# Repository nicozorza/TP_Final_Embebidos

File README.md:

# TP_Final_Embebidos
El TP final de Seminario de Sistemas Embebidos consiste en realizar el control de temperatura para un horno SMD.

###################################################################################################
## Avances con el ADC
* Chip_ADC_Init: Hace una configuracion por default del ADC. Recibe LPC_AD0 o LPC_ADC1, y un puntero a una estructura
	del tipo ADC_CLOCK_SETUP_T que es la que contiene toda la informacion de la configuracion.	
* Chip_ADC_EnableChannel: Habilita un determinado canal del ADC. Recibe LPC_ADC0 o LPC_ADC1, el canal del ADC a utilizar (ADC_CH0-7).
* NVIC_EnableIRQ: Agrega las interrupciones del ADC al vector de interrupciones. Recibe ADC0_IRQn o ADC1_IRQn. 
	El handler es ADC0_IRQHandler o ADC1_IRQHandler.
* Chip_ADC_Int_SetChannelCmd: Habilita o desabilita las interrupciones de un terminado canal del ADC.
* Chip_ADC_SetBurstCmd: Este modo realiza conversiones a maxima velocidad. Apenas termina una conversión comienza otra. Por esta razón,
	si se desean leer los valores convertidos es necesario parar las conversiones en la interrupcion, ya que la velocidad de las
	conversiones no permiten realizar otras actividades (la interrupcion salta todo el tiempo). Este modo permite tambien hacer
	conversiones de todos los canales al mismo tiempo (primero convierte ADC0, luego ADC1 y asi. Convierte los canales activados),
	lo cual evita tener que multiplexar. Hay que tener cuidado porque las sucesivas conversiones se van pisando, asi que hay que 
	leerlas rapido.
* Chip_ADC_SetStartMode: Comienza una conversión del ADC. Permite seleccionar si la conversion quiere hacerse inmediatamente o con
	alguna señal de trigger.
	
### OBSERVACIONES: 
* Usando el StartMode, luego de cada conversión es necesario volver a habilitar el StartMode para realizar una nueva conversión.

###################################################################################################
## Avances con la salida PWM
El bloque PWM tiene 2 salidas (con polaridades opuestas), cada una con 3 canales: MCOA0/1/2 y MCOB0/1/2. Tiene tambien dos canales
de entrada que permiten generar un trigger.
Cada canal tiene un TC(Timer/Counter), el cual es comparado con un "Limit Register", y cuando coinciden, el TC se resetea de dos formas
diferentes:
* En el modo "Edge aligned Mode" el TC se resetea a cero.
* En el modo "Centered Mode" el TC invierte su sentido, y comienza a decrementarse hasta llegar a cero, donde vuelve a incremenetarse.
Cada canal tiene tambien un "Match Register", que tiene un valor menor al Limit Register:
* En el modo "Edge aligned Mode" las salidas se switchean siempre que se alcance el Match o el Limit Register.
* En el modo "Centered Mode" las salidas se switchean unicamente cuando se alcanza el Match Register.

Por lo tanto, el Limit Register controla el periodo mientras que el Match Register el duty cycle.
Al parecer esta libreria no esta implementada, pero lo que si esta es una adaptacion del SCT como PWM. En esta pagina hay información
para configurar el bloque SCT como PWM http://www.lpcware.com/content/faq/how-use-sct-standard-pwm-using-lpcopen. 
Para configurar este bloque se debe hacer:
1) Chip_SCTPWM_Init(LPC_SCT): Habilita un clock externo.
2) Chip_SCTPWM_SetRate(LPC_SCT, SCT_PWM_RATE): Se configura la frecuencia del SCT.
3) Se debe configurar el SCU de los pines a utilizar con Chip_SCU_PinMuxSet(). Las salidas del SCT estan conectadas a los pines 
	CTOUT_n (P4_2, P4_1, P2_10, P4_3, P2_12, P2_11, P1_2, P1_1,...).
4) Configurar el output pin correspondiente con Chip_SCTPWM_SetOutPin(LPC_SCT, index, pin), donde index es un numero que va de 1 a N,
	siendo N la cantidad de pines de salida o de Match Registers (el minimo de los dos), y pin es el pin de CTOUT a configurar.
5) Se configura el duty cycle con Chip_SCTPWM_SetDutyCycle(LPC_SCT, index, ticks), donde ticks indica la cantidad de ticks en que la 
	salida permanece encendida. Utilizando Chip_SCTPWM_PercentageToTicks(LPC_SCT, percent) se puede setear el duty cycle mediante
	porcentajes sobre el total.
6) Se inicia el PWM con Chip_SCTPWM_Start(LPC_SCT).
7) El PWM se detiene con Chip_SCTPWM_Stop(LPC_SCT).

### OBSERVACIONES:
* Chip_SCT_EnableEventInt(LPC_SCT_T *pSCT, CHIP_SCT_EVENT_T evt) permite habilitar las interrupciones de acuerdo a los eventos. El
	handler es SCT_IRQHandler(). Los posibles eventos son: match condition, input o output condition, combinaciones de ambos.
* El tema de las interrupciones no me funciono todavia, pero todo lo otro al parecer funciona perfectamente. Tendria que ver si logro
	hacer andar el pwm de la forma original.
		
###################################################################################################

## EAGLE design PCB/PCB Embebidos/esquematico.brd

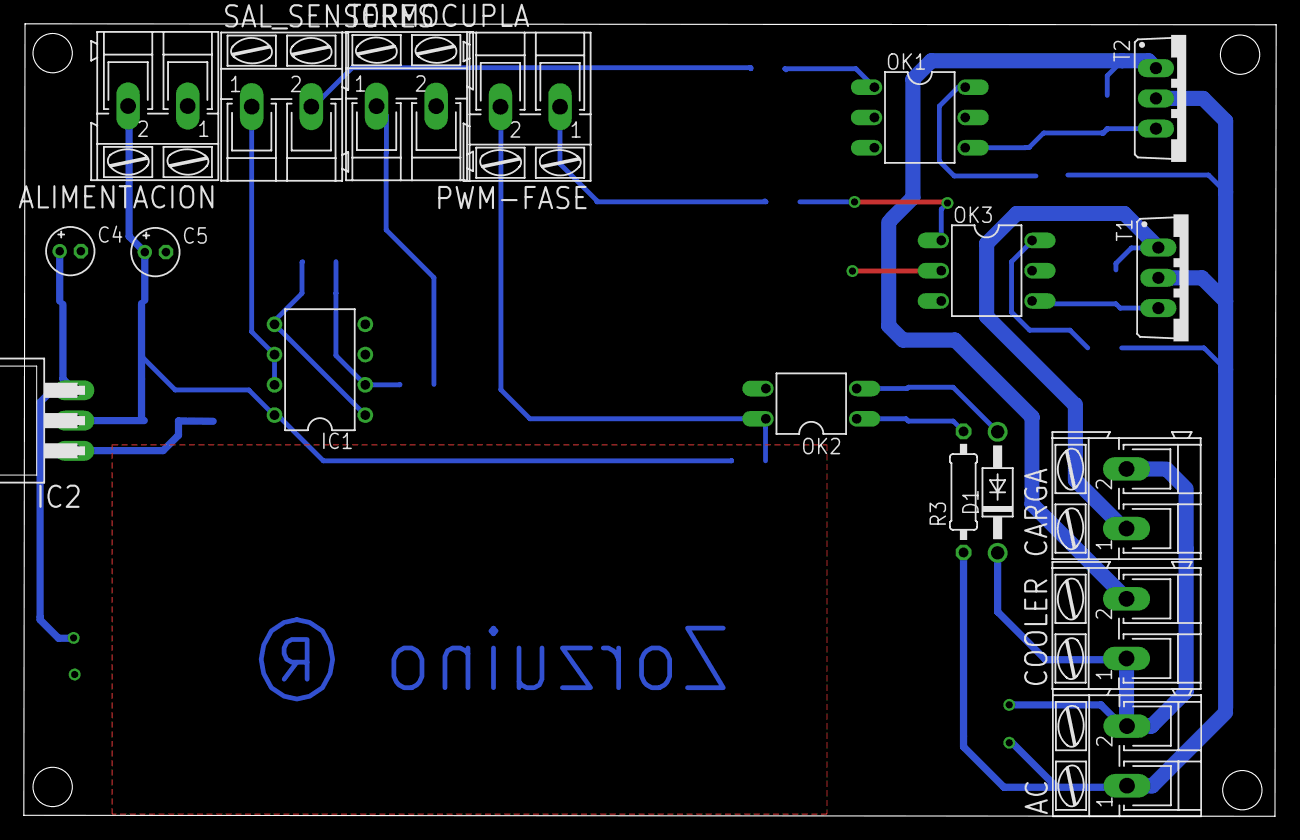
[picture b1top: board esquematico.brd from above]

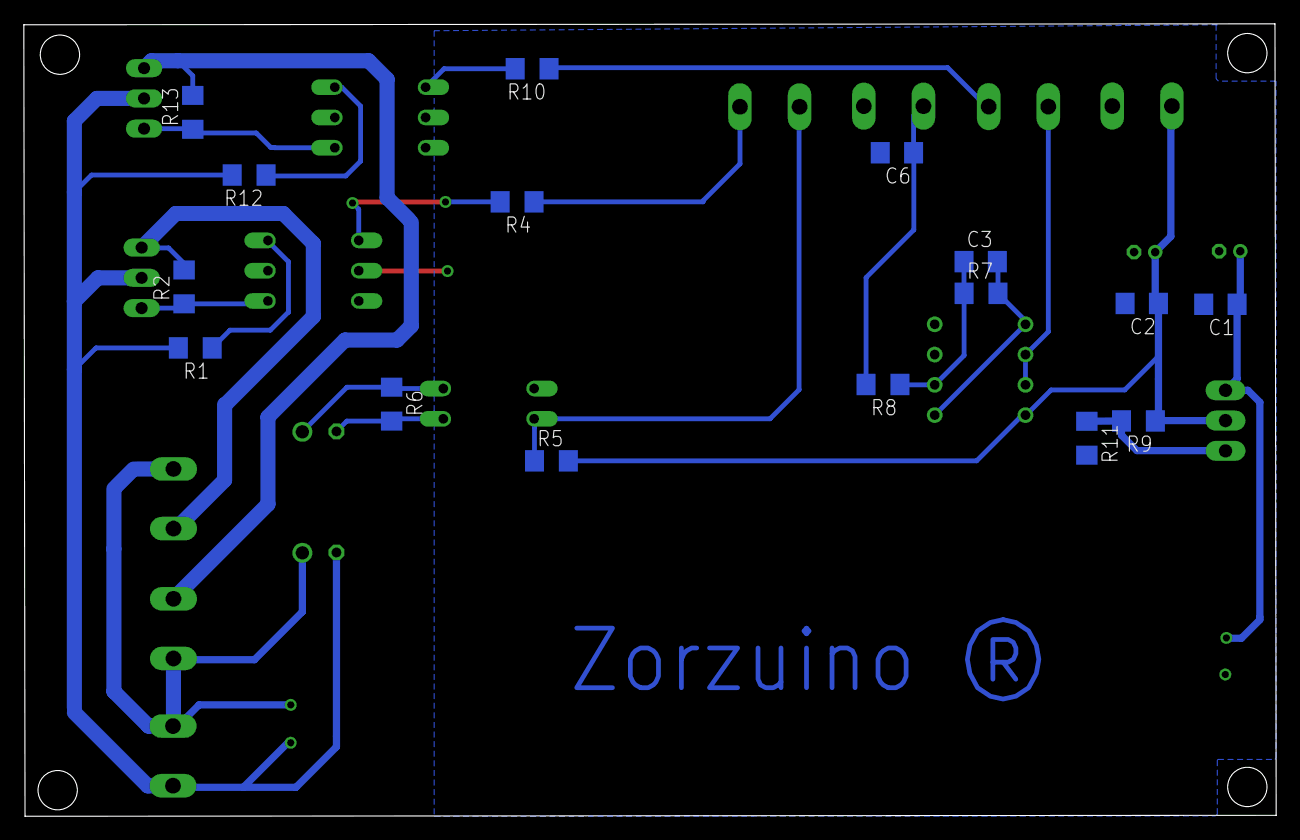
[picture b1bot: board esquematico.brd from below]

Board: 2 copper layers, 105.1 x 66.5 mm, 34 parts (16 on the bottom side), 23 nets.

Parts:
AC: AK300/2
ALIMENTACION: AK300/2
C1, C2, C3, C6: 100n; C1206
C4, C5: 100u; E1,8-4
CARGA: AK300/2
COOLER: AK300/2
D1: 1N4004; DO41-10
IC1: LM358N; DIL08
IC2: 317T; TO220H
OK1, OK3: MOC3031M; DIL06
OK2: PC817; DIL04
PWM-FASE: AK300/2
R1, R2, R12, R13: 330; R1206
R3: 20k; 0207/10
R4, R10: 680; R1206
R5, R8: 1k; R1206
R6: 100k; R1206
R7: 250k; R1206
R9: 340=680/2; R1206
R11: 560; R1206
SAL_SENSORES: AK300/2
T1, T2: BT138-V; TO220BV
TERMOCUPLA: AK300/2

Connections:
AC+: AC.1, R1.2, R3.1, R12.2, T1.T2, T2.T2
AC-: AC.2, CARGA.2, COOLER.1, D1.C
COOLER_PIN: R10.1, SAL_SENSORES.2
FASE: OK2.4, PWM-FASE.2, R5.1
GND: ALIMENTACION.1, C1.2, C2.2, C4.-, C5.-, C6.2, IC1.3, IC1.4, OK1.2, OK2.3, OK3.2, R11.2, TERMOCUPLA.2
unnamed: OK3.1, R4.2
unnamed: OK3.6, R1.1
unnamed: OK2.1, R3.2, R6.2
unnamed: CARGA.1, R2.2, T1.T1
unnamed: C3.1, IC1.2, R7.1, R8.1
unnamed: IC2.1, R9.2, R11.1
unnamed: C3.2, IC1.1, IC1.5, R7.2
unnamed: OK3.4, R2.1, T1.G
unnamed: D1.A, OK2.2, R6.1
unnamed: OK1.1, R10.2
unnamed: OK1.6, R12.1
unnamed: OK1.4, R13.1, T2.G
unnamed: COOLER.2, R13.2, T2.T1
PWM: PWM-FASE.1, R4.1
SAL_TERMOCUPLA: IC1.6, IC1.7, SAL_SENSORES.1
TERMOCUPLA: C6.1, R8.2, TERMOCUPLA.1
VCC: ALIMENTACION.2, C2.1, C5.+, IC1.8, IC2.2, R5.2, R9.1
VCC_5V: C1.1, C4.+, IC2.3

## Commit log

2017-05-05 Empece el proyecto de prueba del puerto serie, donde la idea es armar las librerias para no tener que utilizar DEBUGOUT, etc.
2017-05-05 Hay algun lio con los pines del SCU porque no coinciden con los de la hoja de datos, y por eso solo me anda el UART2 y no los demas
2017-05-06 Empece a probar el ADC. El problema con el puerto serie es que la UART2 es la que esta conectada a la salida USB, entonces para probar los demas puertos de USB tengo que conectar el conversor. Esto l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
2017-05-06 Borro todo porque por alguna razon me quedo todo mal configurado. Vuelvo a empezar
2017-05-06 Probe el ejemplo del adc importado. No encontre porque no me andaba el puerto serie antes, pero mañana lo voy a revisar. Seguro que estoy creando mal el proyecto desde el inicio y por eso explota
2017-05-06 No pude crear un proyecto para probar el ADC desde cero, asi que termine copiando un proyecto ya creado.
2017-05-06 Agrego informacion sobre el BurstMode del ADC
2017-05-06 Empece a probar el pwm. Simplemente importe el ejemplo que hay, pero creo que sin osciloscopio no voy a poder ver bien como funciona. Voy a probar midiendo el valor medio.
2017-05-07 Estuve investigando sobre la generacion de PWM, y agregando datos al readme.md. Estaba viendo sobre el tema de las interrupciones del sct pero me voy a jugar al fulbito
2017-05-08 Al parecer ya anda el PWM (configurandolo segun lo que puse en el README.md). Faltaria averiguar sobre el tema de las interrupciones del pwm y de la otra configuracion que esta en el datasheet. El si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
2017-05-09 Empece a armar un proyecto de prueba para un controlador PID. La idea es poner un pote y ver si funciona: Entro con tension y salgo con pwm. Si esto funciona ya puedo probar de controlar la temperatu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
2017-05-09 Lo que hice fue leer un valor del adc, y utilizarlo para modificar el valor de PWM en un rango entre 0-100%. Esto funciono perfectamente, asi que tengo que ver que onda lo del PID (todavia la placa n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
2017-05-09 Agregue una pequeña simulacion para un controlador PID de tiempo discreto, ya que nunca habia hecho nada de eso. Parece funcionar bien, pero no hice ninguna cuenta asi que esta puesto todo a ojo
2017-05-09 Supuestamente deje todo listo para probar el PID: Hay que cerrar el lazo de realimentacion y ver si funciona. Cuando tenga la bornera hay la prueba posta
2017-05-10 Probe el PID por software y anduvo hermoso. Ahora falta cerrar el lazo de forma física, y ya va a estar todo listo para hacer el control de temperatura
2017-05-10 Modifique unas cositas para que quede mas prolijo el README.md
2017-05-19 Arme los circuitos de deteccion de fase y disparo del tiristor. Cree un proyecto (Prueba_detectar_fase) donde activo las interrupcione de entrada de un pin (para detectar los cruces), meto un delay, 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
2017-05-19 Agregue un proyecto cabeza que utiliza interrupciones en un pin de entrada para sincronizar una senoidal con lo que seria el disparo del gate del triac (Prueba_detectar_fase). Funciono perfectamente,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
2017-05-21 Arme el proyecto Prueba_cambiar_valor_eficaz, donde lo que hago es con un pote variar la tension de un canal del adc, y en funcion de esa tension cambio el valor eficaz de la altera. Para esto lo que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
2017-05-22 Empece a hacer el esquematico. No se si hacer un poncho o una placa separada, porque no me gusta mucho la idea de tener la potencia cerca del micro, a pesar de tener todo con optoacopladores
2017-05-22 Reorganice el proyecto un poco porque estaba todo re tirado
2017-05-22 Empece a escribir el codigo en FreeRTOS. Mas o menos ya pase todo lo que habia hecho antes de forma cabeza, y ahora estoy viendo el tema de la configuracion del timer. Me voy a almorzar y despues sigo
2017-05-22 Modifique algunas cosas en la parte del trigger. Me parece que conviene probar bien todo antes de seguir avanzando, porque me genera dudas los retardos que puede meter el scheduler
2017-05-23 No me habia dado cuenta, pero las librerias que estaba importando tenian la frecuencia del clock dividida por 4. Eso se lo saque, ya que necesito hacer todo a la mayor velocidad posible
2017-05-23 Empece a probar el codigo de FreeRTOS con el circuito. Cada tanto se cuelga, pero no encuentro la razon (el codigo salta a un handler por default, pero lo hace antes de entrar al codigo posta). Esta 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
2017-05-23 No logre ningun resultado positivo con las funciones bloqueantes de FreeRTOS. Ahora esta puesto un delay con un while, pero estuve ajustando algunos numeros para que funcione mejor
2017-05-24 Probe algunas cosas con el sensor de temperatura. Arme un proyectito bien choto que lee el ADC (donde esta conectado el circuito del sensor de temperatura) y lo manda por el puerto serie
2017-05-24 Agregue el circuito de la termocupla al esquematico de Eagle. Falta definir si vamos a meter el PT100 como referencia
2017-05-24 Agregue unas cosas para los sensores de temperatura. No pude hacer bien la calibracion con el pt100, porque ambos sensores miden la misma temperatura (supuestamente la suma de ambas temperaturas da l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
2017-05-24 Agregue al PCB un regulador de 3.3v porque la EDU-CIAA labura con esa tension, y sino iba a tener problemas con el ADC. Tendria que probar que la parte de control siga funcionando bien, pero segun la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
2017-05-25 Estuve probando de hacer el delay del trigger con un timer pero no tuve exito. Cambie un par de macros y emprolije algunas cosas con las pruebas de FreeRTOS
2017-05-26 Cambie las resistencias del PCB a smd. Tambien modifique las borneras para usar unas de 5mm
2017-05-26 Agregue los valores de algunas resistencias que me faltaban, agregue el pt100, y agregue un pdf con una foto del esquematico para poder revisarlo mas facil sin abrir eagle
2017-05-26 Pude hacer el delay que mantiene encendido al trigger con una interrupcion del timer. Tambien agregue una variable global que hace que el valor del ADC se actualice cada 500ms, que es un poco mas raz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
2017-05-26 Reorganice un par de cosas para no tener variables auxiliares al pedo.
2017-05-28 Agregue la tarea del PID. Use las cosas que habia hecho en las pruebas anteriores del PID, pero antes lo habia hecho con pwm, y como ahora es con la temperatura, estoy seguro de como relacionarla con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
2017-05-29 Estuve viendo el tema del controlador. Esta funcionando medio mal, pero no se si es por culpa del software o del hardware. Estoy siguiendo una temperatura de referencia, pero no lo hago demasiado rap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
2017-05-29 Cambie el PID por un P, y parece estar andando bien. Los cambios de temperatura son un poco lentos, pero no se si es por el controlador o porque a la resistencia no le da la potencia. Esta todo medio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
2017-05-30 Cambie todo para usar el controlador proporcional. Estuve emprolijando un poco las cosas. Tendria que empezar a separar las cosas en archivos
2017-05-30 Estuve calibrando un poco los limites del delay del trigger. Tendria que hacerlo con un osciloscopio igual...
2017-05-30 Estuve presentando los componentes en la placa para ver mas o menos como va a quedar
2017-06-01 Agrego el firmware de la EDU-CIAA para tenerlo en el repositorio
2017-06-01 Configure el path del sAPI y ahora compila. Mañana voy a probar si realmente anda o hice cualquier cosa
2017-06-01 El firmware de la edu-ciaa tenia un gitignore que hizo que no se subieran las cosas a mi github. Ahora lo borre y lo tengo de repuesto por si rompo todo
2017-06-01 Logre compilar y debuggear con la sAPI. El proyecto de FreeRTOS que habia hecho se puede usar directamente con la sAPI (falta probarlo, pero compila, asi que seguro anda)
2017-06-01 Estuve probando con sAPI mi codigo de FreeRTOS y parece que anda bien. Tengo que empezar a reemplazar las funciones por las de la sAPI
2017-06-02 Estuve ruteando el PCB. Creo que esta terminado, pero tendria que revisarlo menos dormido
2017-06-02 Me puse a escribir un poco el codigo para un proyecto que en lugar de usar un controlador P, usa un controlador On-Off. No lo pude probar, pero deberia andar. La idea de esto es hacer que se alcance 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
2017-06-04 Tuve unos problemas con las librerias que importe de sAPI, ya que tenian archivos de gitignore que no habia visto. Por culpa de esto perdi todo lo que habia hecho.... Volvi a usar directamente el sof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
2017-06-04 Arregle unas cosas que faltaban, y hacian que los botones de encendido y apagado rompan todo
2017-06-04 Agregue la tarea que va modificando el valor de la referencia con el paso del tiempo. Parece estar funcionando bien, asi que deberia probar haciendo que siga alguna curva especifica (probe con un vec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
2017-06-04 Borre lo del PT100 y agrege las cosas para hacer el control del cooler. Falta ordenar un poco, ver si se puede achicar mas, y volver a rutear
2017-06-04 El PCB esta listo para ser imprimido. Voy a comprar todos los componentes mañana y ya lo termino
2017-06-04 Movi unas cosas para que entren mejor los disipadores
2017-06-10 Tuve que rehacer la placa porque habian quedado muy finas las pistas. El codigo no lo modifique, y parece estar andando todo bien. Mañana le voy a poner disipadores a los triacs y voy a empezar a pon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
2017-06-10 Estuve avanzando un poco con la actualizacion de la referencia de temperatura. Pude seguir una curva de temperatura escalada. La termocupla no esta bien calibrada, asi que mas tarde la voy a volver a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
2017-06-12 Actualice la calibracion de la termocupla
2017-06-12 Estuve jugando con la curva de referencia de temperatura del controlador
2017-06-13 Hice un control proporcional por ciclos enteros para el horno. Funciona mejor que el control on-off
2017-06-13 Agregue unas macros para las prioridades de las tareas
2017-06-13 Corregí el problema que tenia con los botones de apagado y encendido. La funcion vTaskDelayUntil me arruinaba todo, asi que puse vTaskDelay y listo
2017-06-13 Modifique las prioridades de las tareas y un par de cositas mas
2017-06-16 Agregue la tarea tarea que controla el cooler
2017-06-21 Modifique un par de cosas: la ganancia del opamp, los valores de la curva, y un par de detalles mas
2017-06-22 Deje la ultima version que utilizamos, donde uni medio villeramente mi codigo con el de Lio. Agregue tambien las cosas que tenia tiradas en dropbox. El proyecto ya esta terminado, asi que me despido 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
2017-06-22 Me habia olvidado de subir los videos del proyecto
2017-06-22 Habia puesto mal una fecha
